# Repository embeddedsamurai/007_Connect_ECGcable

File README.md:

# Connector between 10 pin and Printerport

## 1. Notice

This Eagle file is a work in progress.
Use of these files is at your own risk.

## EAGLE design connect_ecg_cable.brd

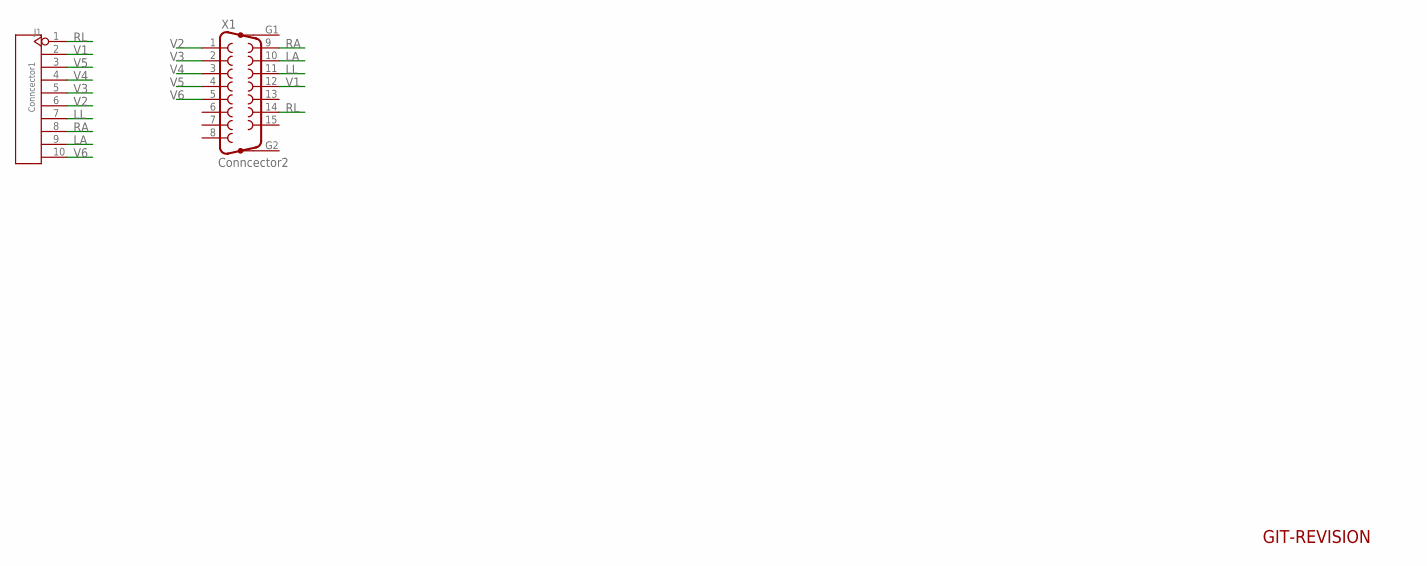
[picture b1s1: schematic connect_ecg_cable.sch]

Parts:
J1: Conncector1; 1X10P-2.54-8.5--BLUE-FEMALE
U$1: GIT-REVISION
X1: Conncector2; F15HP

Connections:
LA: J1.9, X1.10
LL: J1.7, X1.11
RA: J1.8, X1.9
RL: J1.1, X1.14
V1: J1.2, X1.12
V2: J1.6, X1.1
V3: J1.5, X1.2
V4: J1.4, X1.3
V5: J1.3, X1.4
V6: J1.10, X1.5

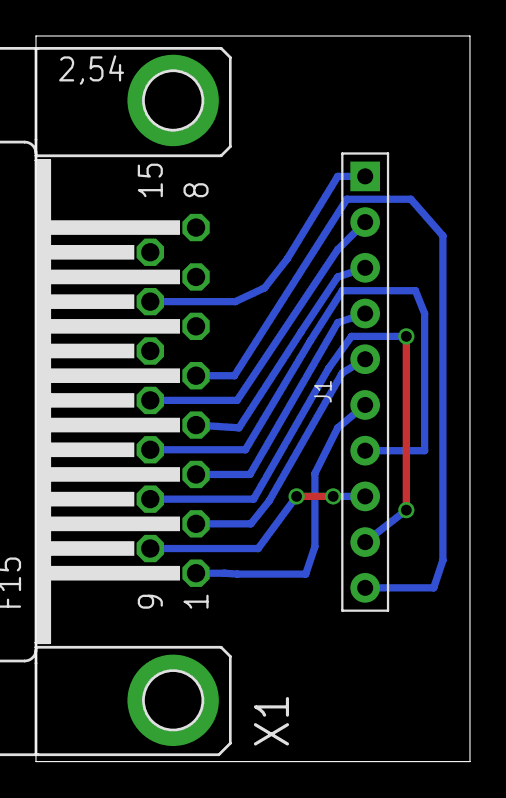
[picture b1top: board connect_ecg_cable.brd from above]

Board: 2 copper layers, 24.1 x 40.3 mm, 3 parts (0 on the bottom side), 10 nets.

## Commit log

2016-05-20 Inital
2016-05-20 add README.md
2016-05-25 did small size about connector
2016-05-25 modify README,md
2016-05-25 outputted garber files
